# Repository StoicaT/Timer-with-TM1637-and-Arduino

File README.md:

# Timer-with-TM1637-and-Arduino
Countdown timer with LED display drive by TM1637 and Arduino Nano.

This countdown timer allows timings in the 1-9999 seconds range. It is built around an Arduino Nano and timer programming is done with a rotary encoder. The display of the duration of the delay and the remaining time is made with LED display module with TM1637.This display is more visible than others I have previously presented, because the numbers are bigger and brighter.

Programming: Set number seconds (rotary encoder) -> push -> secondsX10 -> push -> 100Xseconds -> push -> 1000Xseconds. Now the time is set. The next push will trigger the delay.

During the time delay the load will be powered through the Rel relay. If the MEM button is pressed, no further programming is required, the previous value is retained. More to:
https://www.instructables.com/Timer-With-TM1637-and-Arduino/

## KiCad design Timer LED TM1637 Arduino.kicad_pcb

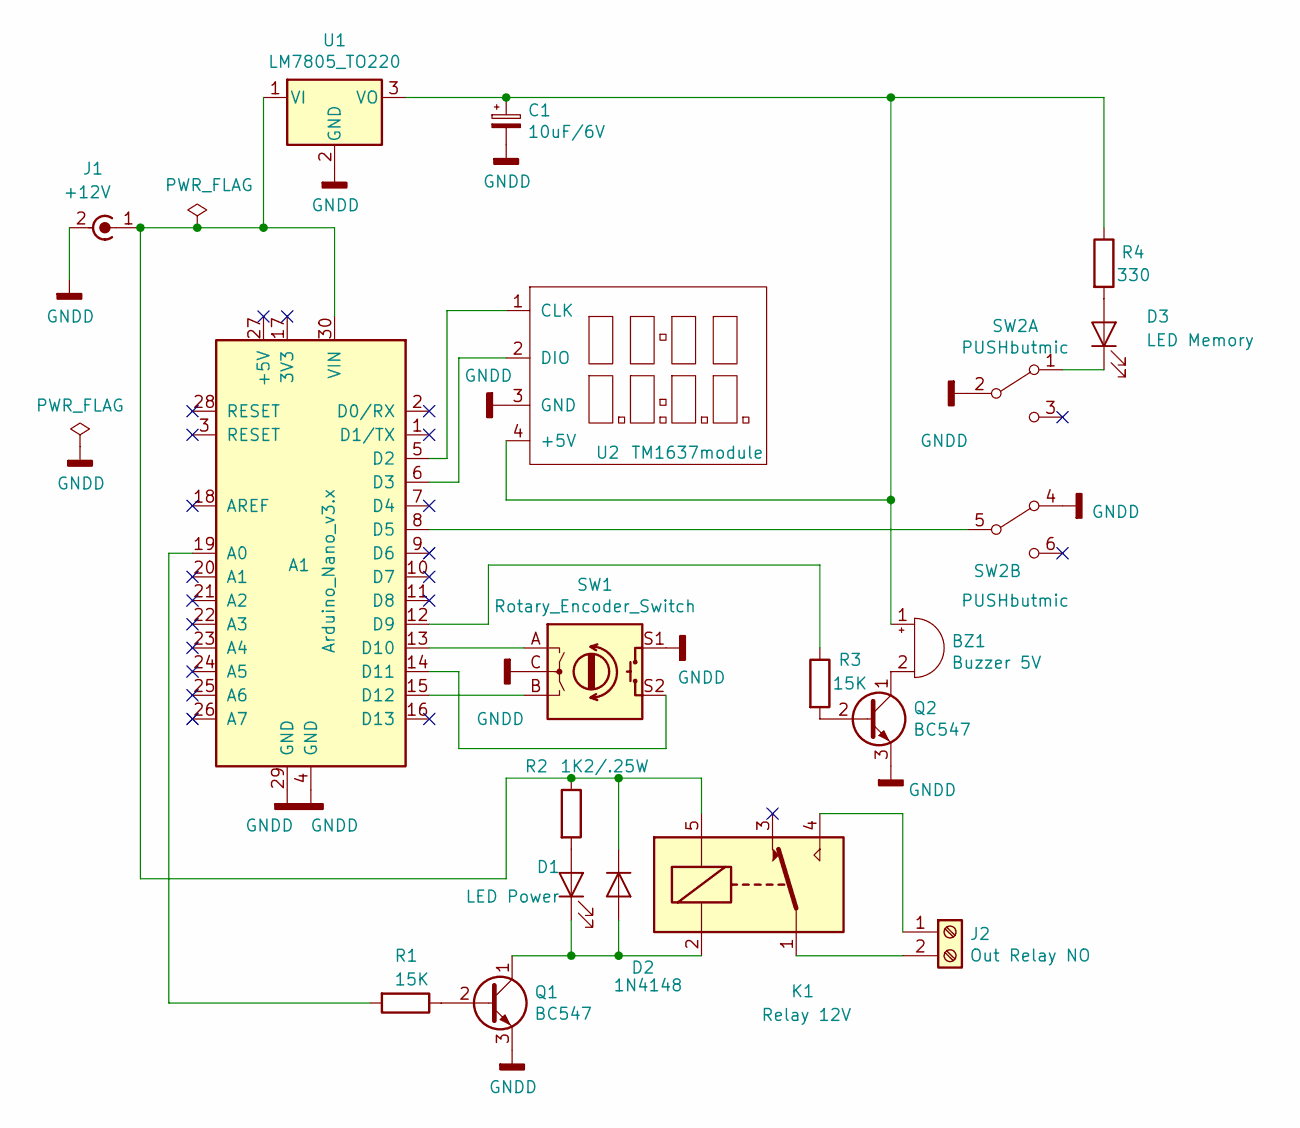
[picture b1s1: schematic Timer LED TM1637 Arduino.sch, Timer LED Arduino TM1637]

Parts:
A1: Arduino_Nano_v3.x; Arduino_Nano
BZ1: Buzzer 5V; Buzzer_12x9.5RM7.6
C1: 10uF/6V; CP_Radial_D5.0mm_P2.50mm
D1: LED Power; LED_D5.0mm
D2: 1N4148; D_DO-35_SOD27_P7.62mm_Horizontal
D3: LED Memory; LED_D5.0mm
J1: +12V; BarrelJack_Horizontal
J2: Out Relay NO; TerminalBlock_MetzConnect_Type094_RT03502HBLU_1x02_P5.00mm_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
K1: Relay 12V; Relay_SPDT_Omron-G5LE-1
Q1, Q2: BC547; TO-92_Inline
R1, R3: 15K; R_Axial_DIN0207_L6.3mm_D2.5mm_P10.16mm_Horizontal
R2: 1K2/.25W; R_Axial_DIN0309_L9.0mm_D3.2mm_P12.70mm_Horizontal
R4: 330; R_Axial_DIN0207_L6.3mm_D2.5mm_P10.16mm_Horizontal
SW1: Rotary_Encoder_Switch; RotaryEncoder_Alps_EC11E-Switch_Vertical_H20mm
SW2: PUSHbutmic; SWlinmic
U1: LM7805_TO220; TO-220-3_Horizontal_TabDown
U2: TM1637module; TM1637 module

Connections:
GNDD: A1.4 (GND), A1.29 (GND), C1.2, J1.2 (Ext), Q1.3 (E), Q2.3 (E), SW1.C, SW1.S1, SW2.2 (B), SW2.4 (A), U1.2 (GND), U2.3 (GND)
unnamed: A1.5 (D2), U2.1 (CLK)
unnamed: A1.6 (D3), U2.2 (DIO)
unnamed: A1.8 (D5), SW2.5 (B)
unnamed: A1.12 (D9), R3.1
unnamed: A1.13 (D10), SW1.A
unnamed: A1.14 (D11), SW1.S2
unnamed: A1.15 (D12), SW1.B
unnamed: A1.19 (A0), R1.2
unnamed: A1.30 (VIN), D2.1 (K), J1.1 (In), K1.5, R2.1, U1.1 (VI)
unnamed: BZ1.1 (-), C1.1, R4.1, U1.3 (VO), U2.4 (+5V)
unnamed: BZ1.2 (+), Q2.1 (C)
unnamed: D1.1 (K), D2.2 (A), K1.2, Q1.1 (C)
unnamed: D1.2 (A), R2.2
unnamed: D3.1 (K), SW2.1 (A)
unnamed: D3.2 (A), R4.2
unnamed: J2.1, K1.4
unnamed: J2.2, K1.1
unnamed: Q1.2 (B), R1.1
unnamed: Q2.2 (B), R3.2

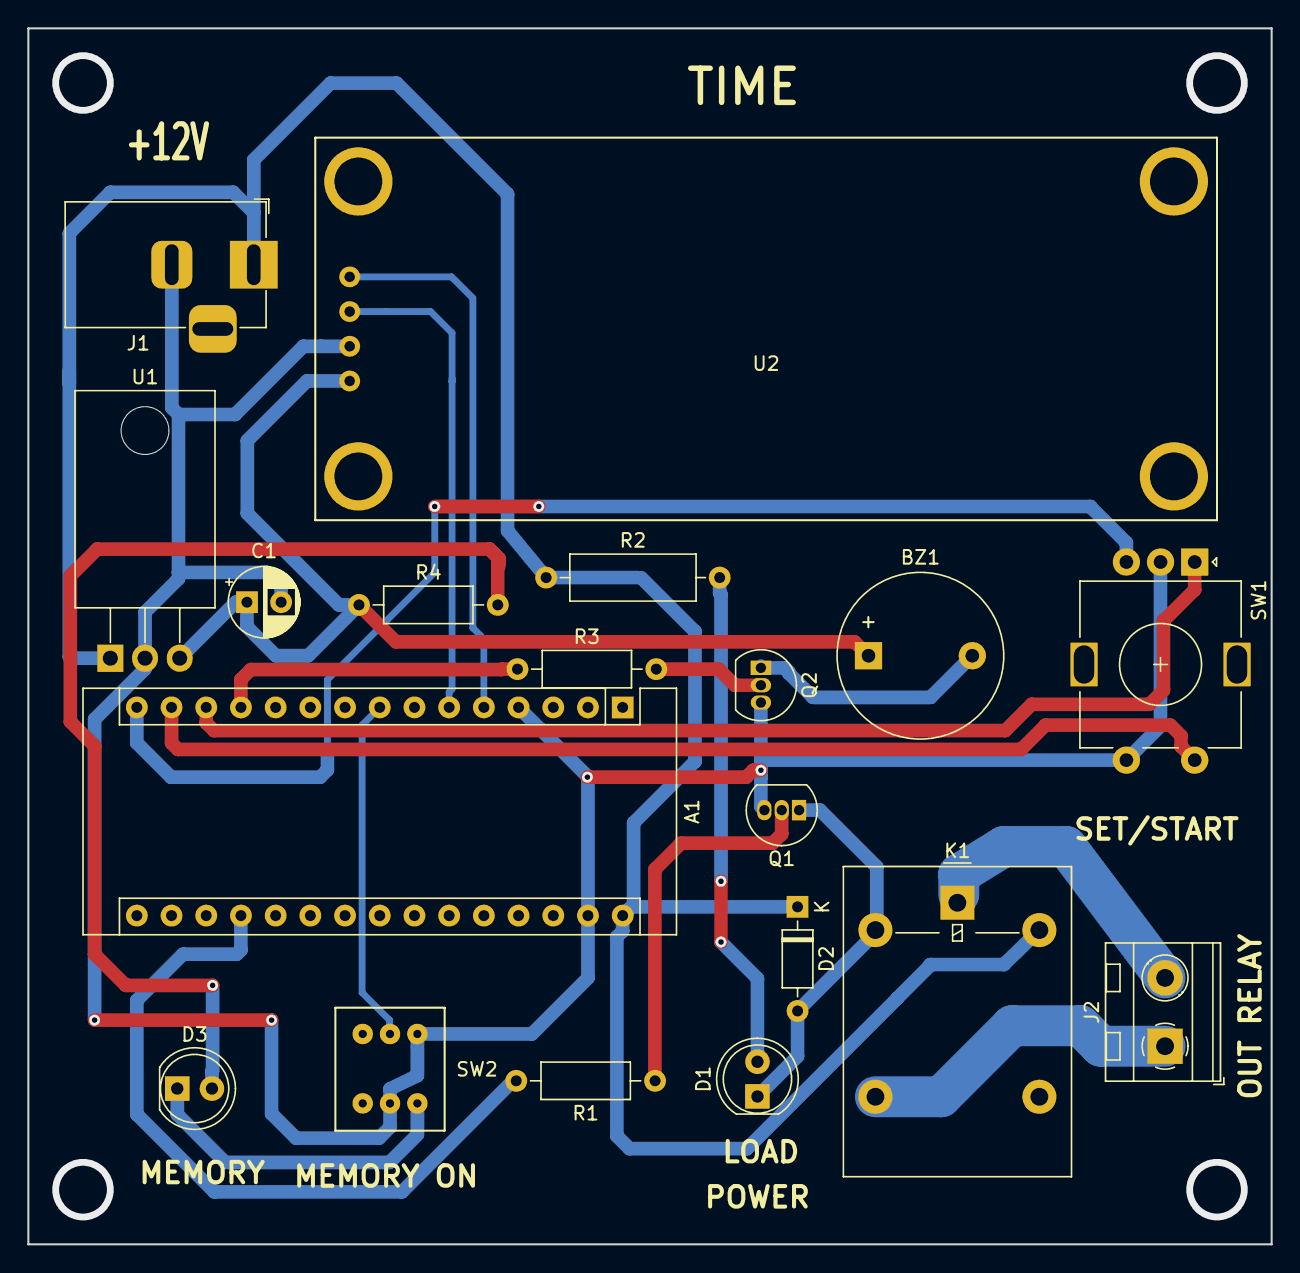
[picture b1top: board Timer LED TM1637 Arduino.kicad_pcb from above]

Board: 2 copper layers, 91.0 x 89.0 mm, 19 parts (0 on the bottom side), 20 nets.
